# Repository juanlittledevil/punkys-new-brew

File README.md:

## Punky's New Brew - Eurorack Drum Module

**Description:**
Punky's New Brew is a Eurorack drum-ish module made from the classic Atari Punk Console circuit. This DIY module produces percussive arcade-style sounds and is perfect for electronic music enthusiasts and synthesizer aficionados. This repository contains the KiCad project files, Gerber files, and other resources related to the construction of the module.

**YouTube Channel:** [Juan's YouTube Channel](https://www.youtube.com/channel/UC0b9VIyAkoUc2IhSYS2gNUg)

**Blog:** [Juan's Blog - Scruffy Cat Studios](scruffycatstudios.com)

For step-by-step instructions on how to build Punky's New Brew and to gain valuable insights into DIY electronics and Eurorack modules, be sure to check out the Scruffy Cat Studios YouTube channel and blog. Dive into the world of modular synthesis and start creating your own unique soundscapes with this punk!

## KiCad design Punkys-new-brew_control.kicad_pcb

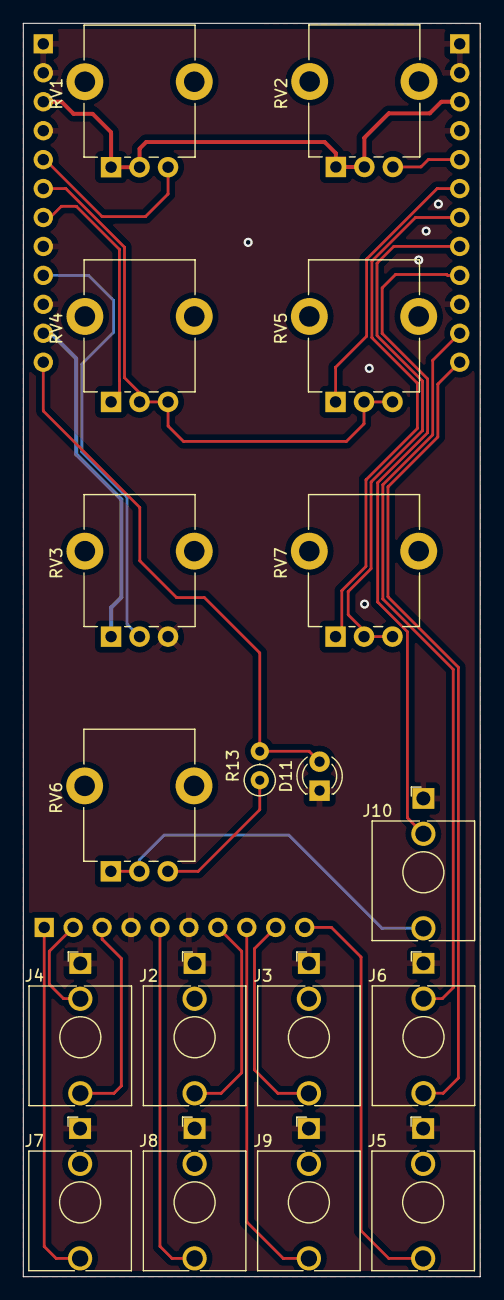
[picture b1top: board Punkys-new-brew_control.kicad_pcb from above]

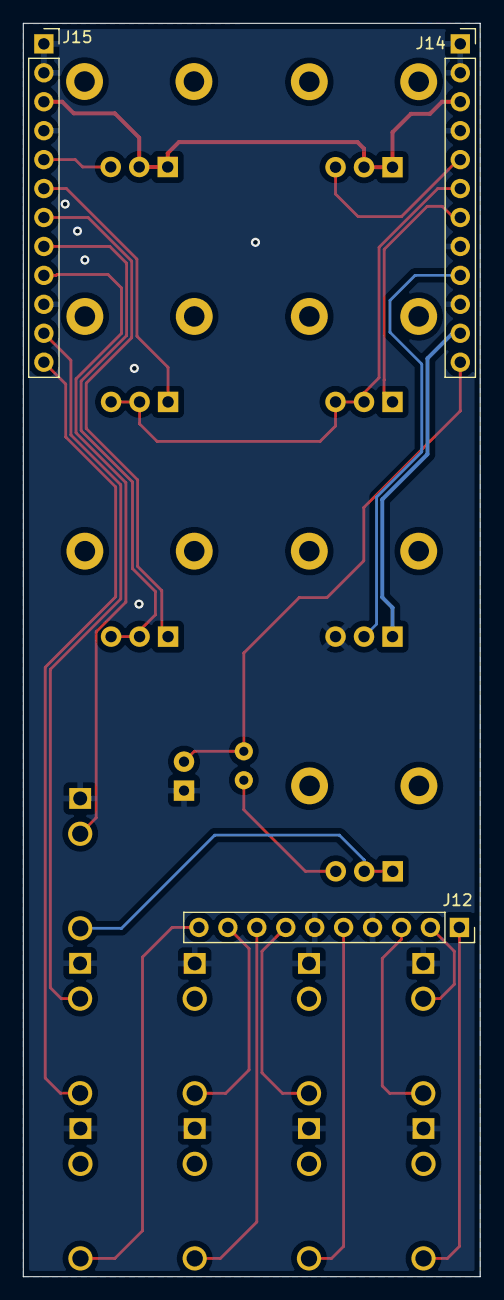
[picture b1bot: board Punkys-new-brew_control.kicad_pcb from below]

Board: 2 copper layers, 40.1 x 110.0 mm, 21 parts (3 on the bottom side), 25 nets.

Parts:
D11: LED; LED_D3.0mm
J2: CV1-In; Jack_3.5mm_QingPu_thonk-PJ398SM_Vertical_CircularHoles
J3: CV2-In; Jack_3.5mm_QingPu_thonk-PJ398SM_Vertical_CircularHoles
J4: Gate-In; Jack_3.5mm_QingPu_thonk-PJ398SM_Vertical_CircularHoles
J5: Audio-Out; Jack_3.5mm_QingPu_thonk-PJ398SM_Vertical_CircularHoles
J6: Ext-Audio; Jack_3.5mm_QingPu_thonk-PJ398SM_Vertical_CircularHoles
J7: ENV1; Jack_3.5mm_QingPu_thonk-PJ398SM_Vertical_CircularHoles
J8: INV_ENV1; Jack_3.5mm_QingPu_thonk-PJ398SM_Vertical_CircularHoles
J9: ENV2; Jack_3.5mm_QingPu_thonk-PJ398SM_Vertical_CircularHoles
J10: VCA-CV; Jack_3.5mm_QingPu_thonk-PJ398SM_Vertical_CircularHoles
J12: 1x10_control; PinSocket_1x10_P2.54mm_Vertical
J14: L_1x12_control; PinSocket_1x12_P2.54mm_Vertical
J15: R_1x12_control; PinSocket_1x12_P2.54mm_Vertical
R13: 1k; R_Axial_DIN0207_L6.3mm_D2.5mm_P2.54mm_Vertical
RV1, RV4, RV5: 1M; Potentiometer_Alpha_RD901F-40-00D_Single_Vertical_CircularH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
RV2, RV3, RV7: 500k; Potentiometer_Alpha_RD901F-40-00D_Single_Vertical_CircularH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
RV6: 100k; Potentiometer_Alpha_RD901F-40-00D_Single_Vertical_CircularH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

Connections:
5V_Ref_C: J4.3, J12.2
10V_REF_C: J14.11, RV3.1
+12V: J14.3, J15.3, RV1.1, RV1.2, RV2.1, RV2.2
APC_Out_C: J6.3, J15.11
Audio_Out_C: J5.2, J12.10
CV1-In_C: J2.2, J12.7
CV2-In_C: J3.2, J12.9
ENV1-Out_C: J7.2, J12.1
ENV1_C: J10.3, J15.9
ENV2_C: J9.2, J12.8
Env1_AR_C: J14.6, RV4.2, RV4.3, RV5.2, RV5.3
Env1_A_C: J14.7, RV4.1
Env1_R_C: J15.6, RV5.1
Env2_AR_C: J15.8, RV7.2, RV7.3
Env2_R_C: J15.7, RV7.1
Ext_In_C: J6.2, J15.12
Freq_1_C: J14.5, RV1.3
Freq_2_C: J15.5, RV2.3
GND: D11.1 (K), J2.1, J3.1, J4.1, J5.1, J6.1, J7.1, J8.1, J9.1, J10.1, J12.4, J12.6, J14.1, J14.2, J14.4, J14.8, J14.10, J15.1, J15.2, J15.4, J15.10, RV3.3
Gate_In_C: J4.2, J12.3
INV_ENV_C: J8.2, J12.5
INV_REF_C: J14.9, RV3.2
unnamed: J10.2, RV6.1, RV6.2
unnamed: R13.1, RV6.3
VCA_CV_C: D11.2 (A), J14.12, R13.2

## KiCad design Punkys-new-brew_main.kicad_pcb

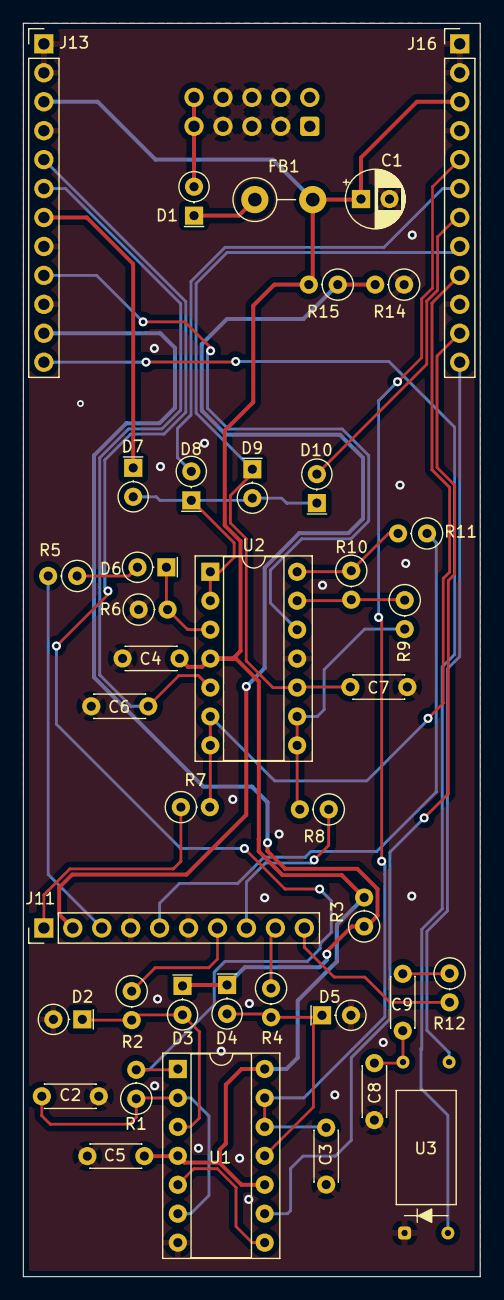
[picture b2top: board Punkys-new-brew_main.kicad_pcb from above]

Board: 2 copper layers, 40.1 x 110.0 mm, 41 parts (1 on the bottom side), 37 nets.

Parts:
C1: C_Polarized_THL; CP_Radial_D5.0mm_P2.50mm
C2: 10nF; C_Disc_D4.3mm_W1.9mm_P5.00mm
C3: 47nF; C_Disc_D4.3mm_W1.9mm_P5.00mm
C4, C5: 100nF; C_Disc_D4.3mm_W1.9mm_P5.00mm
C6, C7, C9: 1uF; C_Disc_D4.3mm_W1.9mm_P5.00mm
C8: 2.2nF; C_Disc_D4.3mm_W1.9mm_P5.00mm
D1, D2, D3, D4, D5: Schottky; D_DO-35_SOD27_P2.54mm_Vertical_KathodeUp
D6, D7, D8, D9, D10: 1N4148; D_DO-35_SOD27_P2.54mm_Vertical_KathodeUp
FB1: FerriteBead; R_Axial_DIN0411_L9.9mm_D3.6mm_P5.08mm_Vertical
J1: +12v; IDC-Header_2x05_P2.54mm_Vertical
J11: 1x10_main; PinHeader_1x10_P2.54mm_Vertical
J13: L_1x12_main; PinHeader_1x12_P2.54mm_Vertical
J16: R_1x12_main; PinHeader_1x12_P2.54mm_Vertical
R1, R2, R4, R5, R7, R8, R11, R12: 1k; R_Axial_DIN0207_L6.3mm_D2.5mm_P2.54mm_Vertical
R3, R6, R9, R10, R14: 100k; R_Axial_DIN0207_L6.3mm_D2.5mm_P2.54mm_Vertical
R15: 140k; R_Axial_DIN0207_L6.3mm_D2.5mm_P2.54mm_Vertical
U1: LM556; DIP-14_W7.62mm_Socket
U2: TL074; DIP-14_W7.62mm_Socket
U3: VTL5C; Vactrol_DIY

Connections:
5V_Ref: J11.2, R14.2, R15.1
10V_REF: D3.1 (K), D4.1 (K), J13.11, R3.1
+12V: C1.1, C4.1, C5.2, FB1.2, J13.3, J16.3, R3.2, R15.2, U1.4 (R), U1.10 (R), U1.14 (VCC), U2.4 (V+)
APC_Out: J16.11, U1.9 (Q)
Audio_Out: J11.10, R12.2
CV1: D2.1 (K), D3.2 (A), R2.2, U1.3 (CV)
CV1-In: J11.7, R2.1
CV2: D4.2 (A), D5.1 (K), R4.2, U1.11 (CV)
CV2-In: J11.9, R4.1
ENV1: J16.9, R7.2, U2.6 (-), U2.7
ENV1-Out: J11.1, R7.1
ENV2: J11.8, R8.1
Env1_A: D7.1 (K), J13.7
Env1_AR: C6.1, J13.6, U2.5 (+)
Env1_R: D8.2 (A), J16.6
Env2_AR: C7.1, D9.1 (K), J16.8, U2.10 (+)
Env2_R: D10.2 (A), J16.7
Ext_In: J16.12, U3.4
Freq_1: J13.5, R1.2, U1.1 (DIS)
Freq_2: C3.1, J16.5, U1.12 (THR), U1.13 (DIS)
GND: C1.2, C2.2, C3.2, C4.2, C5.1, C6.2, C7.2, C8.2, D2.2 (A), D5.2 (A), J1.3 (GND), J1.4 (GND), J1.5 (GND), J1.6 (GND), J1.7 (GND), J1.8 (GND), J11.4, J11.6, J13.1, J13.2, J13.4, J13.8, J13.10, J16.1, J16.2, J16.4, J16.10, R6.1, R14.1, U1.7 (GND), U2.11 (V-), U3.1 (-)
Gate_In: J11.3, R5.2
INV_ENV: J11.5, R11.1
INV_REF: J13.9, U2.12 (+)
unnamed: C8.1, C9.1, U3.3
unnamed: C9.2, R12.1
unnamed: D1.2 (A), J1.9 (12v), J1.10 (12v)
unnamed: D1.1 (K), FB1.1
unnamed: D6.2 (A), R5.1
unnamed: D6.1 (K), R6.2, U2.3 (+)
unnamed: D7.2 (A), D8.1 (K), D9.2 (A), D10.1 (K), U2.1, U2.2 (-)
unnamed: R10.1, R11.2, U2.14
unnamed: U1.5 (Q), U1.8 (TR)
unnamed: C2.1, R1.1, U1.2 (THR), U1.6 (TR)
unnamed: R8.2, R9.2, U2.8, U2.9 (-)
unnamed: R9.1, R10.2, U2.13 (-)
VCA_CV: J13.12, U3.2 (+)

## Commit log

2023-10-27 Enjoy!
2023-10-27 readme
2023-10-27 smaller image.
2023-10-27 smaller even.
2023-10-27 smaller
2023-11-10 fixed some values to better suit my liking. re-routed the invert to env2 instead, it works better me finks.
2023-11-13 update panel gerbers
